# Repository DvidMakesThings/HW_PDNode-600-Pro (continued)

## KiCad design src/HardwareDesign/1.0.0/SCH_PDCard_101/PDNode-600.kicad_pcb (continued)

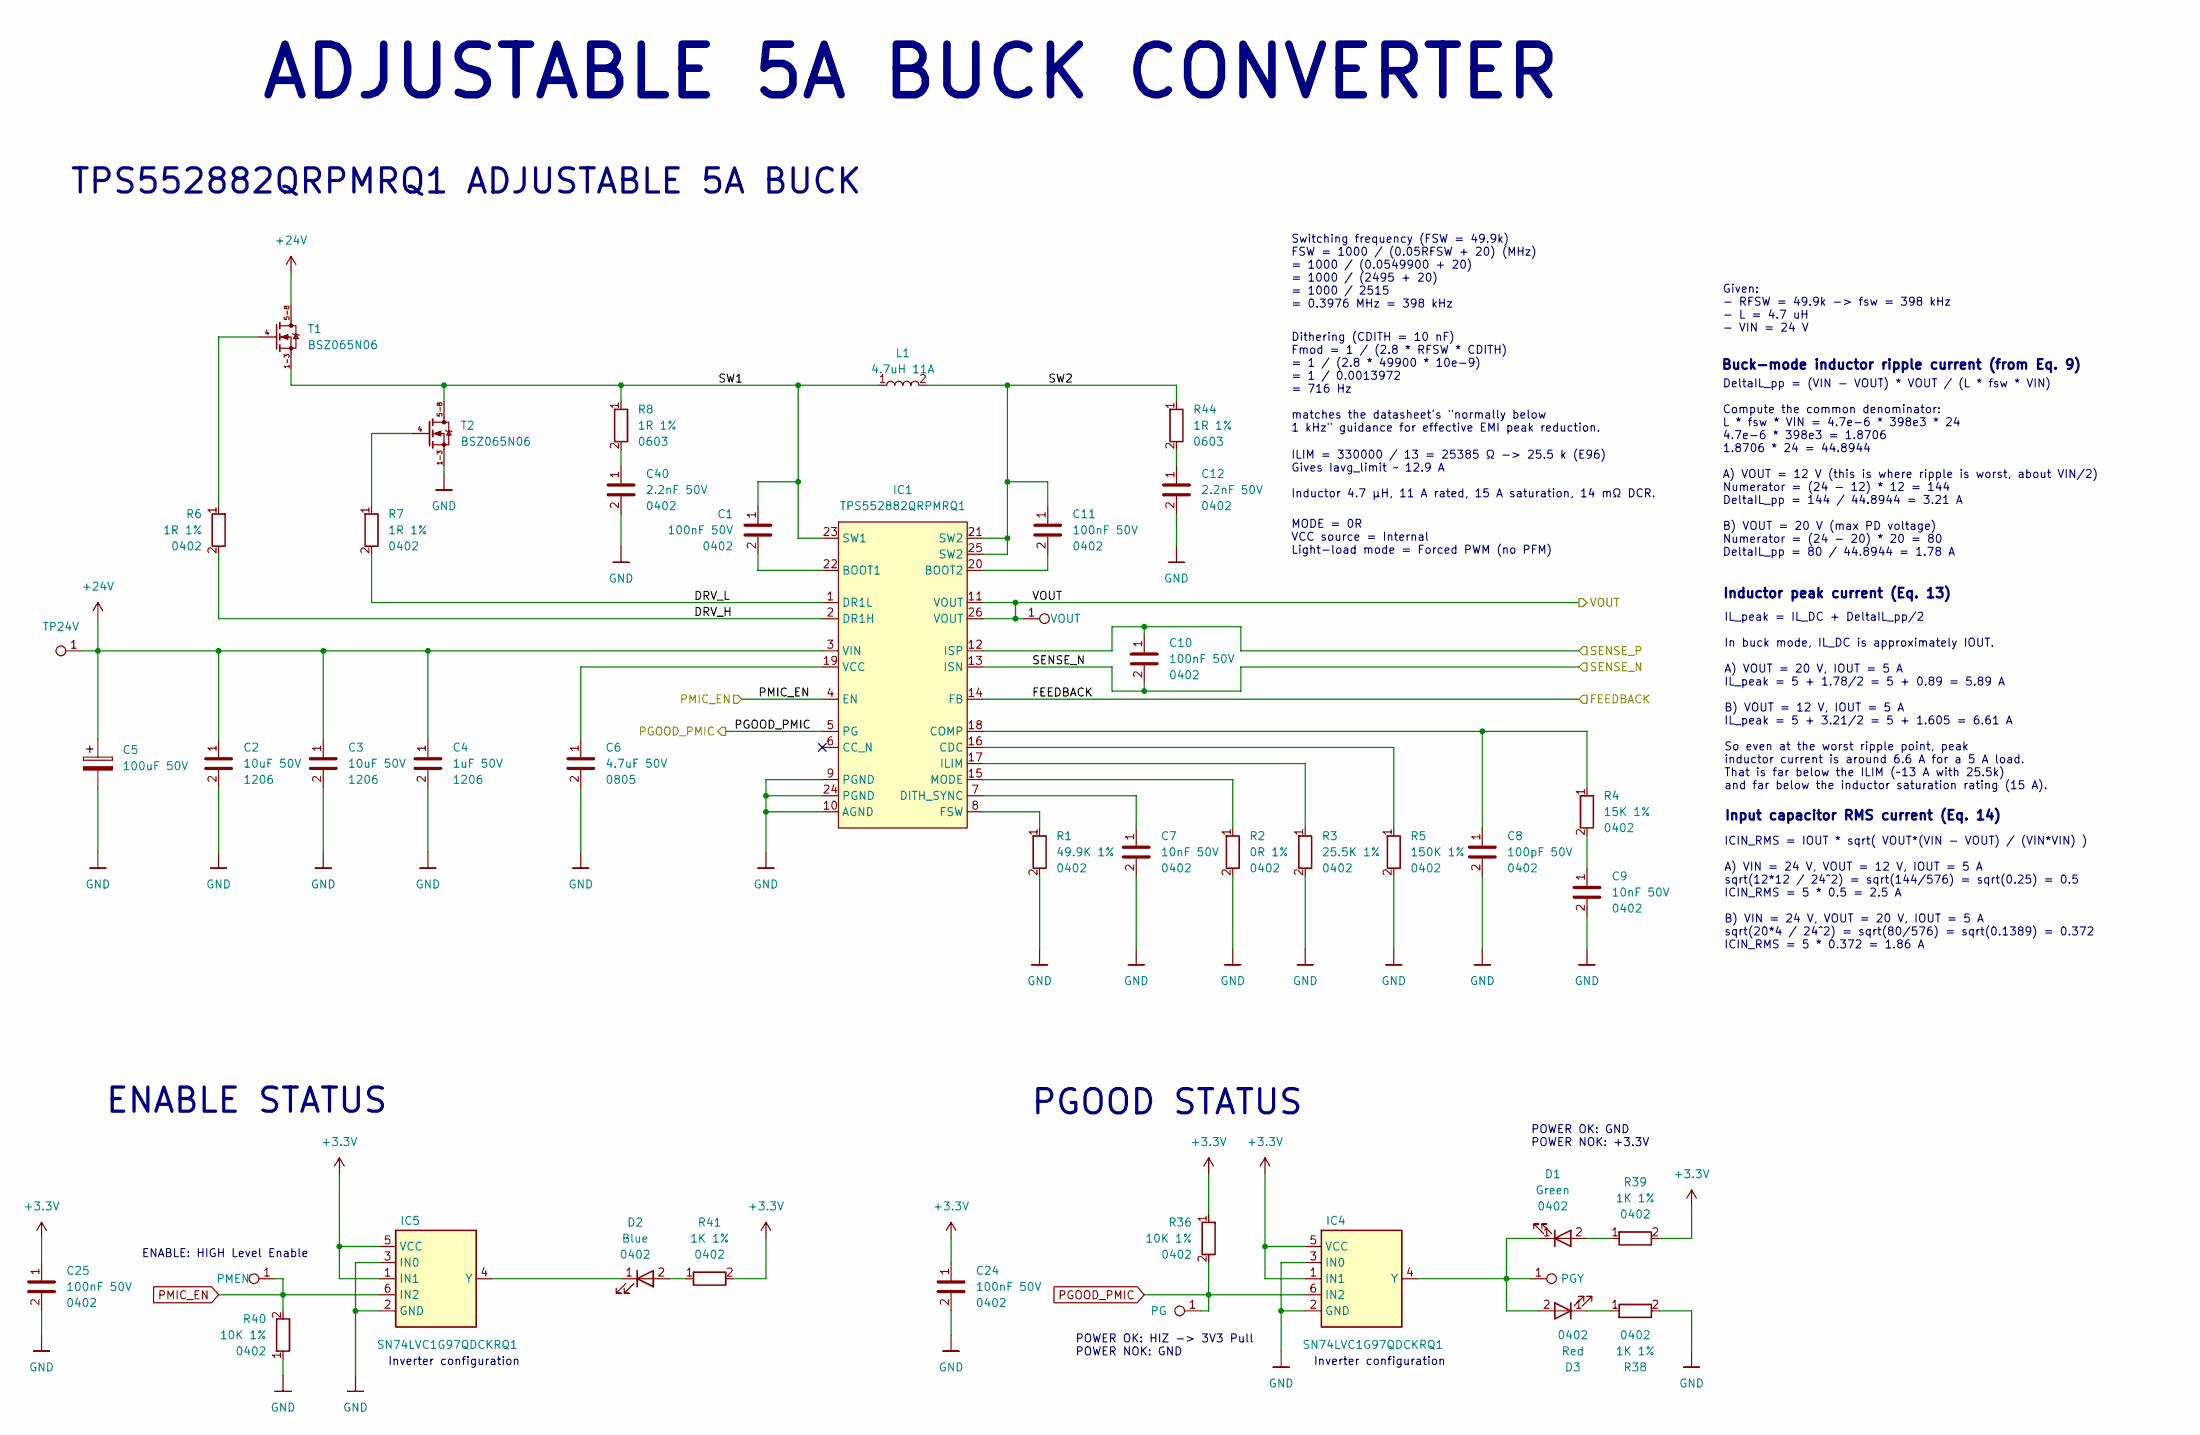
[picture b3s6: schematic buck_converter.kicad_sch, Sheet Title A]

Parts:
C1, C10, C11, C24, C25: 100nF 50V; C_0402_1005Metric; LCSC_PART C307331
C2, C3: 10uF 50V; C_1206_3216Metric; MPN CL31A106KBHNNNE; LCSC_PART C13585
C4: 1uF 50V; C_1206_3216Metric; LCSC_PART C90539
C5: 100uF 50V; C_Elec_6.3x7.7; MPN RVT1H101M0607; LCSC_PART C3151829
C6: 4.7uF 50V; C_0805_2012Metric; MPN CL21A475KBQNNNE; LCSC_PART C98192
C7, C9: 10nF 50V; C_0402_1005Metric; LCSC_PART C60133
C8: 100pF 50V; C_0402_1005Metric; MPN CC0402KRX7R9BB101; LCSC_PART C281751
C12, C40: 2.2nF 50V; C_0402_1005Metric; MPN CC0402KRX7R9BB222; LCSC_PART C106861
D1: Green; LED_0402_1005Metric; MPN XL-1005UGC; LCSC_PART C965793
D2: Blue; LED_0402_1005Metric; MPN XL-1005UBC; LCSC_PART C22355736
D3: Red; LED_0402_1005Metric; MPN XL-1005SURC; LCSC_PART C25503345
IC1: TPS552882QRPMRQ1; PowerVFQFN-26; MPN TPS552882QRPMRQ1; LCSC_PART C2876594
IC4, IC5: SN74LVC1G97QDCKRQ1; SOT-363_SC-70-6; MPN SN74LVC1G97QDCKRQ1; LCSC_PART C179911
L1: 4.7uH 11A; L_11.5x10.0mm; MPN CDRH127NP-4R7NC; LCSC_PART C5359261
PG: TestPoint_0.6mm
PGY: TestPoint_0.6mm
PMEN: TestPoint_0.6mm
R1: 49.9K 1%; R_0402_1005Metric; LCSC_PART C2906873
R2: 0R 1%; R_0402_1005Metric; LCSC_PART C17168
R3: 25.5K 1%; R_0402_1005Metric; LCSC_PART C26970
R4: 15K 1%; R_0402_1005Metric; LCSC_PART C25756
R5: 150K 1%; R_0402_1005Metric; MPN FRC0402F1503TS; LCSC_PART C2909320
R6, R7: 1R 1%; R_0402_1005Metric; MPN RC0402FR-071RL; LCSC_PART C185446
R8, R44: 1R 1%; R_0603_1608Metric
R36, R40: 10K 1%; R_0402_1005Metric; LCSC_PART C25744
R38, R39, R41: 1K 1%; R_0402_1005Metric; LCSC_PART C11702
T1, T2: BSZ065N06; TSDSON-8; MPN BSZ065N06LS5ATMA1; LCSC_PART C6755420
TP24V: TestPoint_0.6mm
VOUT: TestPoint_0.6mm

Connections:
+3.3V: C24.1, C25.1, IC4.1 (IN1), IC4.5 (VCC), IC5.1 (IN1), IC5.5 (VCC), R36.1, R39.2, R41.2; also elsewhere on the board
+24V: C2.1, C3.1, C4.1, C5.1, IC1.3 (VIN), T1.5-8, TP24V.1; also elsewhere on the board
/Block Diagram/Adjustable 5A Buck Converter/DRV_H: IC1.2 (DR1H), R6.2
/Block Diagram/Adjustable 5A Buck Converter/DRV_L: IC1.1 (DR1L), R7.2
/Block Diagram/Adjustable 5A Buck Converter/FEEDBACK: IC1.14 (FB); also elsewhere on the board
/Block Diagram/Adjustable 5A Buck Converter/SENSE_N: C10.2, IC1.13 (ISN); also elsewhere on the board
/Block Diagram/Adjustable 5A Buck Converter/SENSE_P: C10.1, IC1.12 (ISP); also elsewhere on the board
/Block Diagram/Adjustable 5A Buck Converter/SW1: C1.1, IC1.23 (SW1), L1.1, R8.1, T1.1-3, T2.5-8
/Block Diagram/Adjustable 5A Buck Converter/SW2: C11.1, IC1.21 (SW2), IC1.25 (SW2), L1.2, R44.1
/Block Diagram/Adjustable 5A Buck Converter/VOUT: IC1.11 (VOUT), IC1.26 (VOUT), VOUT.1; also elsewhere on the board
GND: C2.2, C3.2, C4.2, C5.2, C6.2, C7.2, C8.2, C9.2, C12.2, C24.2, C25.2, C40.2, IC1.9 (PGND), IC1.10 (AGND), IC1.24 (PGND), IC4.2 (GND), IC4.3 (IN0), IC5.2 (GND), IC5.3 (IN0), R1.2, R2.2, R3.2, R5.2, R38.2, R40.1, T2.1-3; also elsewhere on the board
unnamed: C9.1, R4.2
unnamed: C12.1, R44.2
unnamed: C40.1, R8.2
unnamed: D1.2, R39.1
unnamed: D2.2, R41.1
unnamed: D3.1, R38.1
unnamed: C1.2, IC1.22 (BOOT1)
unnamed: C11.2, IC1.20 (BOOT2)
unnamed: IC1.16 (CDC), R5.1
unnamed: C8.1, IC1.18 (COMP), R4.1
unnamed: C7.1, IC1.7 (DITH_SYNC)
unnamed: IC1.8 (FSW), R1.1
unnamed: IC1.17 (ILIM), R3.1
unnamed: IC1.15 (MODE), R2.1
unnamed: C6.1, IC1.19 (VCC)
unnamed 61: D1.1, D3.2, IC4.4 (Y), PGY.1; also elsewhere on the board
unnamed: D2.1, IC5.4 (Y)
unnamed: R6.1, T1.4
unnamed: R7.1, T2.4
PGOOD_PMIC: IC1.5 (PG), IC4.6 (IN2), PG.1, R36.2; also elsewhere on the board
PMIC_EN: IC1.4 (EN), IC5.6 (IN2), PMEN.1, R40.2; also elsewhere on the board

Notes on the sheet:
ENABLE STATUS
ILIM = 330000 / 13 = 25385 Ω -> 25.5 k (E96) Gives Iavg_limit ~ 12.9 A
IL_peak = IL_DC + DeltaIL_pp/2 In buck mode, IL_DC is approximately IOUT. A) VOUT = 20 V, IOUT = 5 A IL_peak = 5 + 1.78/2 = 5 + 0.89 = 5.89 A B) VOUT = 12 V, IOUT = 5 A IL_peak = 5 + 3.21/2 = 5 + 1.605 = 6.61 A So even at the worst ripple point, peak inductor current is around 6.6 A for a 5 A load.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
Input capacitor RMS current (Eq. 14)
POWER OK: GND POWER NOK: +3.3V
MODE = 0R VCC source = Internal Light-load mode = Forced PWM (no PFM)
POWER OK: HIZ -> 3V3 Pull POWER NOK: GND
Inductor peak current (Eq. 13)
DeltaIL_pp = (VIN - VOUT) * VOUT / (L * fsw * VIN) Compute the common denominator: L * fsw * VIN = 4.7e-6 * 398e3 * 24 4.7e-6 * 398e3 = 1.8706 1.8706 * 24 = 44.8944 A) VOUT = 12 V (this is where ripple is worst, about VIN/2) Numerator = (24 - 12) * 12 = 144 DeltaIL_pp = 144 / 44.8944 = 3.21 A B) VO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
TPS552882QRPMRQ1 ADJUSTABLE 5A BUCK
Dithering (CDITH = 10 nF) Fmod = 1 / (2.8 * RFSW * CDITH) = 1 / (2.8 * 49900 * 10e-9) = 1 / 0.0013972 = 716 Hz matches the datasheet's "normally below 1 kHz" guidance for effective EMI peak reduction.
Inductor 4.7 µH, 11 A rated, 15 A saturation, 14 mΩ DCR.
ICIN_RMS = IOUT * sqrt( VOUT*(VIN - VOUT) / (VIN*VIN) ) A) VIN = 24 V, VOUT = 12 V, IOUT = 5 A sqrt(12*12 / 24^2) = sqrt(144/576) = sqrt(0.25) = 0.5 ICIN_RMS = 5 * 0.5 = 2.5 A B) VIN = 24 V, VOUT = 20 V, IOUT = 5 A sqrt(20*4 / 24^2) = sqrt(80/576) = sqrt(0.1389) = 0.372 ICIN_RMS = 5 * 0.372 = 1.86 A
Buck-mode inductor ripple current (from Eq. 9)
PGOOD STATUS
Given: - RFSW = 49.9k -> fsw = 398 kHz - L = 4.7 uH - VIN = 24 V
ENABLE: HIGH Level Enable
Inverter configuration
Switching frequency (FSW = 49.9k) FSW = 1000 / (0.05RFSW + 20) (MHz) = 1000 / (0.0549900 + 20) = 1000 / (2495 + 20) = 1000 / 2515 = 0.3976 MHz = 398 kHz
ADJUSTABLE 5A BUCK CONVERTER

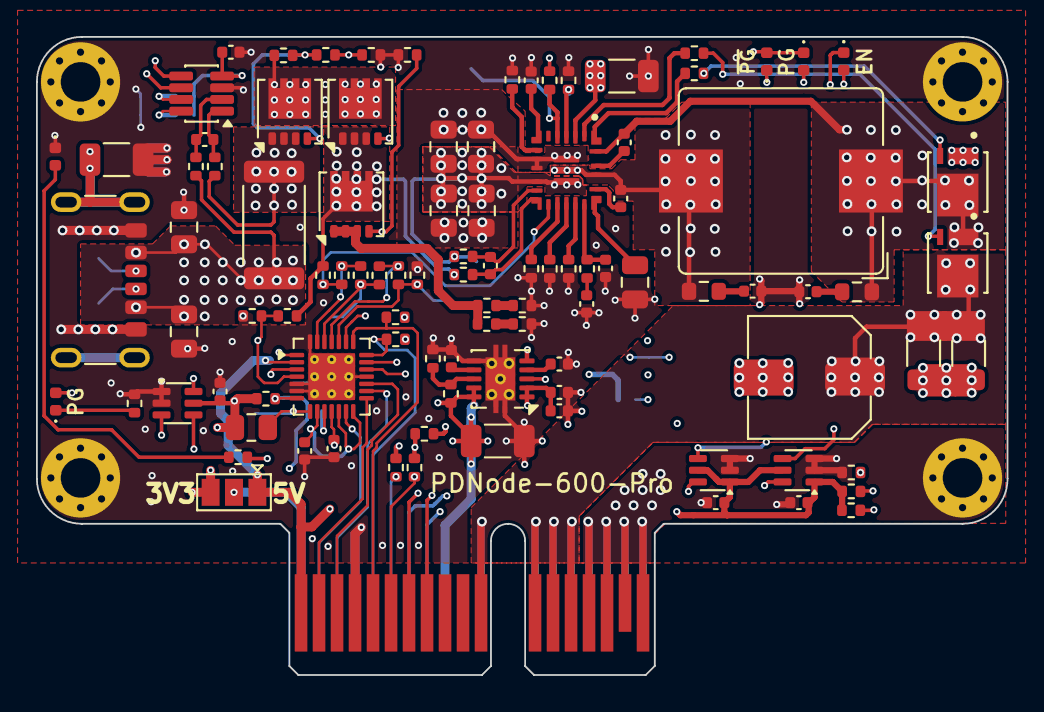
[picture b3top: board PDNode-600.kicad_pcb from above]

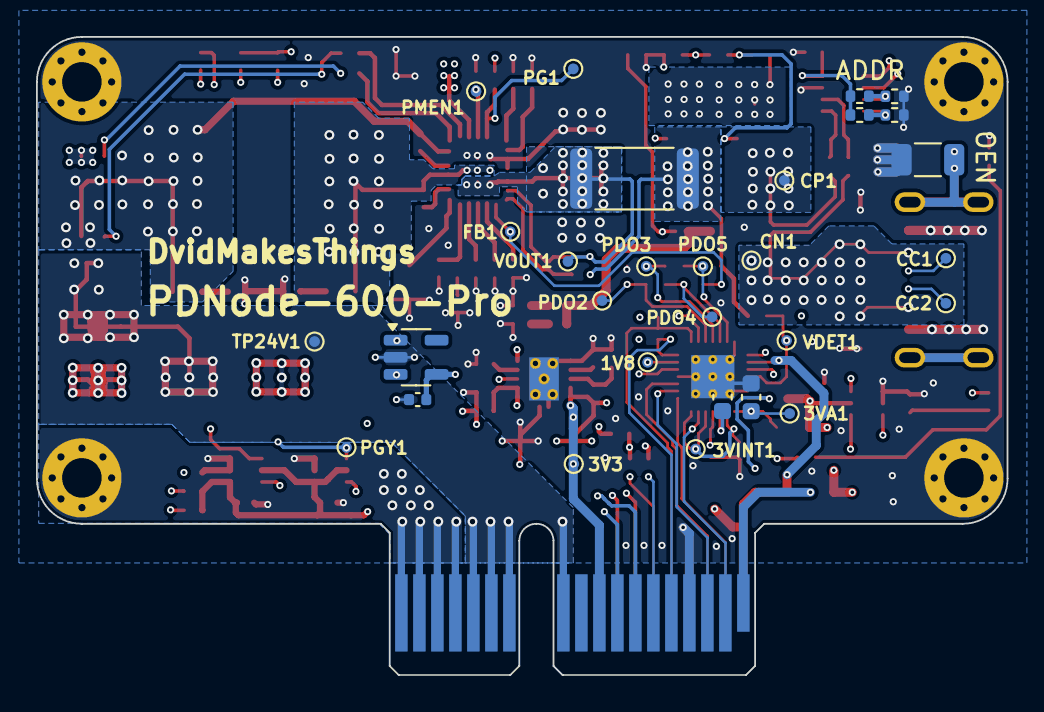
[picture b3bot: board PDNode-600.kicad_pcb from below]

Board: 6 copper layers, 53.9 x 35.5 mm, 132 parts (29 on the bottom side), 76 nets.

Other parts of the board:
3VINT1: TestPoint_0.6mm
CN1: TestPoint_0.6mm
CP1: TestPoint_0.6mm
PG1: TestPoint_0.6mm
PGY1: TestPoint_0.6mm
PMEN1: TestPoint_0.6mm
TP24V1: TestPoint_0.6mm
VDET1: TestPoint_0.6mm
VOUT1: TestPoint_0.6mm

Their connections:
+24V: TP24V1.1; also elsewhere on the board
/Block Diagram/Adjustable 5A Buck Converter/VOUT: VOUT1.1; also elsewhere on the board
/Block Diagram/USB-PD Source Controller/3V3_INTERNAL: 3VINT1.1; also elsewhere on the board
/Block Diagram/USB-PD Source Controller/CURR_MEA: CP1.1; also elsewhere on the board
/Block Diagram/USB-PD Source Controller/VBUS_DET: VDET1.1; also elsewhere on the board
unnamed 61: PGY1.1; also elsewhere on the board
PGOOD_PMIC: PG1.1; also elsewhere on the board
PMIC_EN: PMEN1.1; also elsewhere on the board
VBUS: CN1.1; also elsewhere on the board

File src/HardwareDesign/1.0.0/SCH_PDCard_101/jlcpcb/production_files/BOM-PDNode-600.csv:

Comment,Designator,Footprint,LCSC,Quantity
0.010R 1%,"R27,R9",R_2512_6332Metric,C127692,2
0R 1%,"R10,R11,R2",R_0402_1005Metric,C17168,3
100nF 50V,"C1,C10,C11,C18,C22,C24,C25,C30,C32,C41",C_0402_1005Metric,C307331,10
100pF 50V,C8,C_0402_1005Metric,C281751,1
100uF 50V,C5,C_Elec_6.3x7.7,C3151829,1
10K 1%,"R13,R14,R15,R16,R17,R18,R19,R30,R31,R34,R35,R36,R37,R40,R48,R50,R51",R_0402_1005Metric,C25744,17
10R 1%,"R28,R29",R_0402_1005Metric,C25077,2
10nF 50V,"C7,C9",C_0402_1005Metric,C60133,2
10uF 50V,"C2,C29,C3",C_1206_3216Metric,C13585,3
12.7K 1%,R21,R_0402_1005Metric,C25853,1
150K 1%,R5,R_0402_1005Metric,C2909320,1
15K 1%,R4,R_0402_1005Metric,C25756,1
1K 1%,"R38,R39,R41,R46,R49",R_0402_1005Metric,C11702,5
1M 1%,R26,R_1206_3216Metric,C17927,1
1R 1%,"R6,R7",R_0402_1005Metric,C185446,2
1nF 2kV,C23,C_1206_3216Metric,C173242,1
1uF 50V,"C21,C26,C27",C_0402_1005Metric,C1518208,3
1uF 50V,C4,C_1206_3216Metric,C90539,1
2.2nF 50V,"C12,C28,C40",C_0402_1005Metric,C106861,3
2.2uF 50V,"C19,C20",C_0603_1608Metric,C913904,2
2.4K 1%,R42,R_0402_1005Metric,C25882,1
200K 1%,R20,R_0402_1005Metric,C25764,1
22uF 35V,"C13,C14,C15,C16,C17,C39",C_0805_2012Metric,C6119901,6
25.5K 1%,R3,R_0402_1005Metric,C26970,1
30.9K 1%,R25,R_0402_1005Metric,C270615,1
4.64K 1%,"R22,R23",R_0402_1005Metric,C5153956,2
4.7uF 50V,C6,C_0805_2012Metric,C98192,1
4.7uH 11A,L1,L_11.5x10.0mm,C5359261,1
49.9K 1%,R1,R_0402_1005Metric,C2906873,1
7.5K 1%,R43,R_0402_1005Metric,C25918,1
8.87K 1%,R24,R_0402_1005Metric,C48391747,1
90.9K 1%,R12,R_0402_1005Metric,C163452,1
BLM21BD121SN1D,L3,R_0805_2012Metric,C1235333,1
BSZ065N06,"T1,T2",TSDSON-8,C6755420,2
Blue,"D2,D4",LED_0402_1005Metric,C22355736,2
DMP3013SFV,"T3,T4,T5",Diodes_PowerDI3333-8,C264098,3
Green,"D1,D5",LED_0402_1005Metric,C965793,2
INA219BIDCNT,IC3,SOT-23-8,C2653868,1
MCP22350T-2I/Q8X,IC2,QFN-28-1EP_4x4mm_P0.4mm_EP2.6x2.6mm_ThermalVias,C38202699,1
Red,D3,LED_0402_1005Metric,C25503345,1
SN74LVC1G97QDCKRQ1,"IC4,IC5,IC7",SOT-363_SC-70-6,C179911,3
TPS552882QRPMRQ1,IC1,PowerVFQFN-26,C2876594,1
TPS74801DRCT,IC6,VSON-10-1EP_3x3mm_P0.5mm_EP1.65x2.4mm_ThermalVias,C882845,1
USB_C_Receptacle_PowerOnly_6P,J1,USB_C_Receptacle_GCT_USB4125-xx-x-0190_6P_TopMnt_Horizontal,C2927029,1

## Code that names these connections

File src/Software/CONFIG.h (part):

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/* -------------------------------------------------------------------------- */
/*  I2C0 - Onboard EEPROM (AT24C256) + M.2 connector                         */
/* -------------------------------------------------------------------------- */
#define PIN_I2C0_SDA 32 /* I2C0 data  (4.7K pull-up)         */
#define PIN_I2C0_SCL 33 /* I2C0 clock (4.7K pull-up)         */

/* -------------------------------------------------------------------------- */
/*  W5500 Ethernet Control                                                    */
/* -------------------------------------------------------------------------- */
#define PIN_ETH_RST 34 /* W5500 hardware reset              */
#define PIN_ETH_INT 35 /* W5500 interrupt (active low)      */

/* -------------------------------------------------------------------------- */
/*  Onboard Heartbeat LED                                                     */
/* -------------------------------------------------------------------------- */
#define PIN_HEARTBEAT 36 /* Blue LED, 100R series resistor    */

/* -------------------------------------------------------------------------- */
/*  ADC - Onboard                                                             */
/* -------------------------------------------------------------------------- */
#define PIN_ADC_VUSB 46 /* GPIO46/ADC6 - USB VBUS sense (5.1K-5.1K divider) */
#define PIN_ADC_VREF 47 /* GPIO47/ADC7 - 3.00V 0.1% ref (10K-10K divider)   */

/* -------------------------------------------------------------------------- */
/*  Unused GPIOs - M.2 Connector (directly accent through M.2 edge connector) */
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#define PD_IRQ_EVENT_B2 1 /* MCP23017T INT-B USB-A Signal */
#define PIN_I2C1_SDA 2    /* M.2 pin 53 - I2C1 data  (MCP23017) */
#define PIN_I2C1_SCL 3    /* M.2 pin 51 - I2C1 clock (MCP23017) */
#define SPI_MISO 4        /* SPI0 MISO */
#define SPI_CS 5          /* SPI0 CS */
#define SPI_CLK 6         /* SPI0 CLK */
#define SPI_MOSI 7        /* SPI0 MOSI */
#define SPI_CS_PORT7 8    /* PDCard SPI0 CS7 */
#define SPI_CS_PORT6 9    /* PDCard SPI0 CS6 */
#define SPI_CS_PORT5 10   /* PDCard SPI0 CS5 */
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#define SPI_CS_PORT0 15   /* PDCard SPI0 CS0 */
#define PIN_5V_BUCK_EN 16 /* TPS51225CRUKR 5V Buck Enable */
#define PGOOD_SYSPMIC 17  /* TPS51225CRUKR Power Good */
// #define PIN_GPIO18            18      /* M.2 pin 17 - Unused */
#define PAC_ALERT_P23 19    /* PAC1720 Alert Channel 2-3 */
#define PAC_ALERT_P01 20    /* PAC1720 Alert Channel 0-1 */
#define PIN_MUX_S3 21       /* MUX Select 3 */
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#define PD_IRQ_EVENT_A 26   /* MCP23017T INT-A MCPAddr: 0x23 */
#define PD_IRQ_EVENT_B 27   /* MCP23017T INT-B MCPAddr: 0x23 */

/* GPIO37, GPIO38, GPIO39 are NOT connected on BladeCore-M54E */
#ifdef PIN_GPIO37
#error "GPIO37 is not connected on BladeCore-M54E"
#endif
#ifdef PIN_GPIO38
#error "GPIO38 is not connected on BladeCore-M54E"
#endif
#ifdef PIN_GPIO39
#error "GPIO39 is not connected on BladeCore-M54E"
#endif

#define PIN_ADC_24V 40           /* 24V Input Voltage */
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/* -------------------------------------------------------------------------- */
/*  Heartbeat LED - PWM configuration                                         */
/* -------------------------------------------------------------------------- */
/*  GPIO36 -> PWM slice 2, channel A (RP2354B: slice = (gpio >> 1) & 0xF)    */
#define HEARTBEAT_PWM_FREQ_HZ 1000
#define HEARTBEAT_FADE_STEP_MS 8

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#define PMIC_VMON_PORT2 5  /* CD74HC4067 channel 5 - PMIC VMON */
#define PMIC_VMON_PORT1 6  /* CD74HC4067 channel 6 - PMIC VMON */
#define PMIC_VMON_PORT0 7  /* CD74HC4067 channel 7 - PMIC VMON */
#define VBUS_VMON_PORT0 8  /* CD74HC4067 channel 8  - VBUS VMON */
#define VBUS_VMON_PORT1 9  /* CD74HC4067 channel 9  - VBUS VMON */
#define VBUS_VMON_PORT2 10 /* CD74HC4067 channel 10 - VBUS VMON */
#define VBUS_VMON_PORT3 11 /* CD74HC4067 channel 11 - VBUS VMON */
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#define W5500_MISO PIN_ETH_MISO
#define W5500_SCK PIN_ETH_SCK
#define W5500_CS PIN_ETH_CS
#define W5500_RESET PIN_ETH_RST
#define W5500_INT PIN_ETH_INT

/* ethernet_driver.c gets the rest of its defines from ethernet_config.h */

/* ========================================================================= */
/*  I2C Bus Compatibility Defines                                             */
/* ========================================================================= */
#define I2C0_SDA PIN_I2C0_SDA
#define I2C0_SCL PIN_I2C0_SCL
#define I2C0_SPEED EEPROM_I2C_BAUDRATE
#define I2C1_SDA PIN_I2C1_SDA
#define I2C1_SCL PIN_I2C1_SCL
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#define ENABLE_NET_TASK 1       /* W5500 Ethernet + HTTP + SNMP           */
#define ENABLE_PDCARD_TASK 1    /* USB-C PD port monitoring               */
#define ENABLE_USBA_TASK 1      /* USB-A port monitoring                  */
#define ENABLE_HEARTBEAT_TASK 1 /* Heartbeat LED                          */
#define ENABLE_HEALTH_TASK 1    /* Watchdog + per-task liveness monitor   */

/* ========================================================================= */
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
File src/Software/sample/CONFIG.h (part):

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#define UART0_TX 1
#define I2C1_SDA 2
#define I2C1_SCL 3
#define I2C0_SDA 4
#define I2C0_SCL 5
#define GPIO6 6   // Not used anymore
#define GPIO7 7   // Not used anymore
#define GPIO8 8   // Not used anymore
#define GPIO9 9   // Not used anymore
#define GPIO10 10 // Not used anymore
#define GPIO11 11 // Not used anymore
#define KEY_0 12
#define KEY_1 13
#define KEY_2 14
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#define MCP_MB_RST 23
#define MCP_DP_RST 24
#define VREG_EN 25
#define ADC_VUSB 26
#define NC 27 // ADC Temp sensor (not used)
#define PROC_LED 28
#define ADC_12V_MEA 29
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/** @name ADC Channels
 * @ingroup config01
 * @{ */
#define ADC_VREF 3.0f
#define ADC_MAX 4096.0f
#define ADC_TOL 1.005f // +0.5% correction factor
#define V_USB 0
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
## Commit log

2025-05-02 Start hardware design
2025-05-05 Hardware design update
2025-05-06 Update hardware design files
2025-05-07 Add BOM
2025-05-22 Update RESET and BOOT part values in hardware design files
2025-09-08 Update licensing to protect hardware components
2026-02-04 Project ramp-up: KiCad transition. Board redesign
2026-02-05 update component lib
2026-02-05 Baseboard design start
2026-02-09 Add bladecore to design
2026-02-13 add datasheets
2026-02-17 almost finished baseboard
2026-02-17 M54 rework
2026-02-24 baseboard development
2026-02-26 add PDCard-4242 with lower profile
2026-02-27 hardware design is close to final status
2026-02-27 add folder structure
2026-02-27 add playground
2026-02-27 fix background transient issue
2026-03-01 update readme, add documentation
2026-03-06 finalized 1.0.0 revision, PCB, PCBA ordered
2026-03-30 minor fixes, start with software
2026-03-30 add provisioning
2026-03-30 fix current reading bug
